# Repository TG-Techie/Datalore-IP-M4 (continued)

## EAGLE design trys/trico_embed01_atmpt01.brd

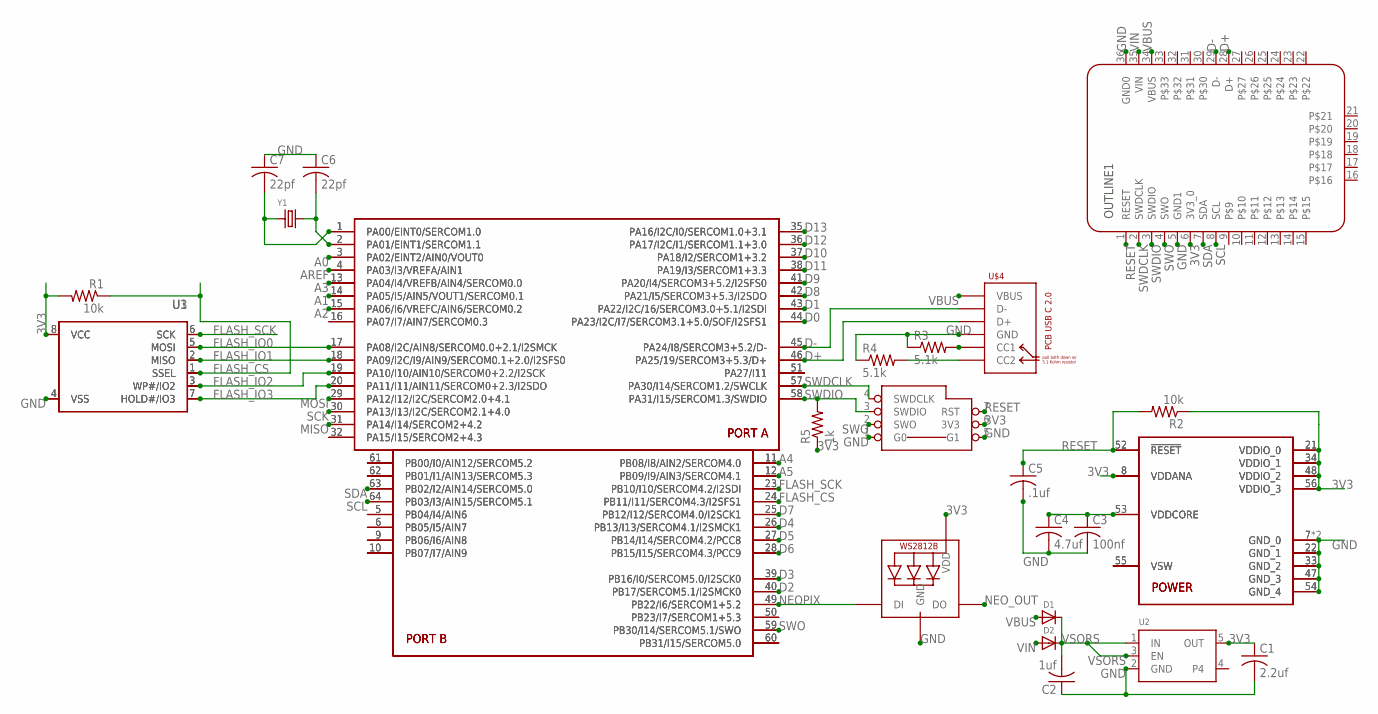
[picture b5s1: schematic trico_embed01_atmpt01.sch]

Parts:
C1: 2.2uf; TG-C0805MP
C2: 1uf; TG-C0805MP
C3: 100nf; TG-C0805MP
C4: 4.7uf; TG-C0805MP
C5: .1uf; TG-C0805MP
C6, C7: 22pf; TG-C0805MP
D1, D2: DIODESOD-123; SOD-123
LED1: LED-NEO-WS2812B3535; LED3535
OUTLINE1: TRIOC_DEV_36_EMBED_01BREAK; TRICO_DEV_01_BRK_HYBRID
R1, R2: 10k; TG-R0805
R3, R4: 5.1k; TG-R0805
R5: 1k; TG-R0805
U1: FLASH-SPI-SOIC8; SOIC8_150MIL
U2: VREG_STD_MIN_SOT23-5; SOT23-5
U3: FLASH-SPI-SOIC8208MIL; SOIC8_208MIL
U$1: MCU-ATSAMD51J-ADATQFP; QFP50P1200X1200X120-64N
U$2: MCU-ATSAMD51J-ADAADA; MICROBUILDER_PQFN64-1
U$3: SWD_POGO
U$4: USB-C-PCB-USB-2.0-TYPE-CDS_2; USB_TYPE_C_DS_2
Y1: XTAL_ADA4.9X1.8; MICROBUILDER_CRYSTAL_4.9X1.8

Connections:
3V3: C1.1, LED1.2 (VDD), OUTLINE1.6 (3V3_0), R1.2, R2.1, R5.1, U1.8 (VCC), U2.5 (OUT), U3.8 (VCC), U$1.8 (VDDANA), U$1.21 (VDDIO_0), U$1.34 (VDDIO_1), U$1.48 (VDDIO_2), U$1.56 (VDDIO_3), U$2.8 (VDDANA), U$2.21 (VDDIO_0), U$2.34 (VDDIO_1), U$2.48 (VDDIO_2), U$2.56 (VDDIO_3), U$3.6 (3V3)
A0: U$1.3 (PA02/EINT2/AIN0/VOUT0), U$2.3 (PA02/EINT2/AIN0/VOUT0)
A1: U$1.14 (PA05/I5/AIN5/VOUT1/SERCOM0.1), U$2.14 (PA05/I5/AIN5/VOUT1/SERCOM0.1)
A2: U$1.15 (PA06/I6/VREFC/AIN6/SERCOM0.2), U$2.15 (PA06/I6/VREFC/AIN6/SERCOM0.2)
A3: U$1.13 (PA04/I4/VREFB/AIN4/SERCOM0.0), U$2.13 (PA04/I4/VREFB/AIN4/SERCOM0.0)
A4: U$1.11 (PB08/I8/AIN2/SERCOM4.0), U$2.11 (PB08/I8/AIN2/SERCOM4.0)
A5: U$1.12 (PB09/I9/AIN3/SERCOM4.1), U$2.12 (PB09/I9/AIN3/SERCOM4.1)
AREF: U$1.4 (PA03/I3/VREFA/AIN1), U$2.4 (PA03/I3/VREFA/AIN1)
CC1: R3.2, U$4.A5 (CC1)
CC2: R4.2, U$4.B5 (CC2)
D0: U$1.44 (PA23/I2C/I7/SERCOM3.1+5.0/SOF/I2SFS1), U$2.44 (PA23/I2C/I7/SERCOM3.1+5.0/SOF/I2SFS1)
D1: U$1.43 (PA22/I2C/16/SERCOM3.0+5.1/I2SDI), U$2.43 (PA22/I2C/16/SERCOM3.0+5.1/I2SDI)
D2: U$1.40 (PB17/SERCOM5.1/I2SMCK0), U$2.40 (PB17/SERCOM5.1/I2SMCK0)
D3: U$1.39 (PB16/I0/SERCOM5.0/I2SCK0), U$2.39 (PB16/I0/SERCOM5.0/I2SCK0)
D4: U$1.26 (PB13/I13/SERCOM4.1/I2SMCK1), U$2.26 (PB13/I13/SERCOM4.1/I2SMCK1)
D5: U$1.27 (PB14/I14/SERCOM4.2/PCC8), U$2.27 (PB14/I14/SERCOM4.2/PCC8)
D6: U$1.28 (PB15/I15/SERCOM4.3/PCC9), U$2.28 (PB15/I15/SERCOM4.3/PCC9)
D7: U$1.25 (PB12/I12/SERCOM4.0/I2SCK1), U$2.25 (PB12/I12/SERCOM4.0/I2SCK1)
D8: U$1.42 (PA21/I5/SERCOM3+5.3/I2SDO), U$2.42 (PA21/I5/SERCOM3+5.3/I2SDO)
D9: U$1.41 (PA20/I4/SERCOM3+5.2/I2SFS0), U$2.41 (PA20/I4/SERCOM3+5.2/I2SFS0)
D10: U$1.37 (PA18/I2/SERCOM1+3.2), U$2.37 (PA18/I2/SERCOM1+3.2)
D11: U$1.38 (PA19/I3/SERCOM1+3.3), U$2.38 (PA19/I3/SERCOM1+3.3)
D12: U$1.36 (PA17/I2C/I1/SERCOM1.1+3.0), U$2.36 (PA17/I2C/I1/SERCOM1.1+3.0)
D13: U$1.35 (PA16/I2C/I0/SERCOM1.0+3.1), U$2.35 (PA16/I2C/I0/SERCOM1.0+3.1)
D+: OUTLINE1.28 (D+), U$1.46 (PA25/19/SERCOM3+5.3/D+), U$2.46 (PA25/19/SERCOM3+5.3/D+), U$4.A6 (D+), U$4.B6 (D+)
D-: OUTLINE1.29 (D-), U$1.45 (PA24/I8/SERCOM3+5.2/D-), U$2.45 (PA24/I8/SERCOM3+5.2/D-), U$4.A7 (D-), U$4.B7 (D-)
FLASH_CS: R1.1, U1.1 (SSEL), U3.1 (SSEL), U$1.24 (PB11/I11/SERCOM4.3/I2SFS1), U$2.24 (PB11/I11/SERCOM4.3/I2SFS1)
FLASH_IO0: U1.5 (MOSI), U3.5 (MOSI), U$1.17 (PA08/I2C/AIN8/SERCOM0.0+2.1/I2SMCK), U$2.17 (PA08/I2C/AIN8/SERCOM0.0+2.1/I2SMCK)
FLASH_IO1: U1.2 (MISO), U3.2 (MISO), U$1.18 (PA09/I2C/I9/AIN9/SERCOM0.1+2.0/I2SFS0), U$2.18 (PA09/I2C/I9/AIN9/SERCOM0.1+2.0/I2SFS0)
FLASH_IO2: U1.3 (WP#/IO2), U3.3 (WP#/IO2), U$1.19 (PA10/I10/AIN10/SERCOM0+2.2/I2SCK), U$2.19 (PA10/I10/AIN10/SERCOM0+2.2/I2SCK)
FLASH_IO3: U1.7 (HOLD#/IO3), U3.7 (HOLD#/IO3), U$1.20 (PA11/I11/AIN11/SERCOM0+2.3/I2SDO), U$2.20 (PA11/I11/AIN11/SERCOM0+2.3/I2SDO)
FLASH_SCK: U1.6 (SCK), U3.6 (SCK), U$1.23 (PB10/I10/SERCOM4.2/I2SDI), U$2.23 (PB10/I10/SERCOM4.2/I2SDI)
GND: C1.2, C2.1, C3.2, C4.2, C5.2, C6.1, C7.1, LED1.4 (GND), OUTLINE1.5 (GND1), OUTLINE1.36 (GND0), R3.1, R4.1, U1.4 (VSS), U2.2 (GND), U3.4 (VSS), U$1.7 (GND_0), U$1.22 (GND_1), U$1.33 (GND_2), U$1.47 (GND_3), U$1.54 (GND_4), U$2.7 (GND_0), U$2.22 (GND_1), U$2.33 (GND_2), U$2.47 (GND_3), U$2.54 (GND_4), U$2.EXP (GND_0), U$3.1 (G0), U$3.5 (G1), U$4.A1 (GND), U$4.A12 (GND), U$4.B1 (GND), U$4.B12 (GND)
MISO: U$1.31 (PA14/I14/SERCOM2+4.2), U$2.31 (PA14/I14/SERCOM2+4.2)
MOSI: U$1.29 (PA12/I12/I2C/SERCOM2.0+4.1), U$2.29 (PA12/I12/I2C/SERCOM2.0+4.1)
unnamed: U$1.16 (PA07/I7/AIN7/SERCOM0.3), U$2.16 (PA07/I7/AIN7/SERCOM0.3)
unnamed: U$1.32 (PA15/I15/SERCOM2+4.3), U$2.32 (PA15/I15/SERCOM2+4.3)
unnamed: U$1.51 (PA27/I11), U$2.51 (PA27/I11)
unnamed: U$1.61 (PB00/I0/AIN12/SERCOM5.2), U$2.61 (PB00/I0/AIN12/SERCOM5.2)
unnamed: U$1.62 (PB01/I1/AIN13/SERCOM5.3), U$2.62 (PB01/I1/AIN13/SERCOM5.3)
unnamed: U$1.5 (PB04/I4/AIN6), U$2.5 (PB04/I4/AIN6)
unnamed: U$1.6 (PB05/I5/AIN7), U$2.6 (PB05/I5/AIN7)
unnamed: U$1.9 (PB06/I6/AIN8), U$2.9 (PB06/I6/AIN8)
unnamed: U$1.10 (PB07/I7/AIN9), U$2.10 (PB07/I7/AIN9)
unnamed: U$1.50 (PB23/I7/SERCOM1+5.3), U$2.50 (PB23/I7/SERCOM1+5.3)
unnamed: U$1.60 (PB31/I15/SERCOM5.0), U$2.60 (PB31/I15/SERCOM5.0)
unnamed: U$1.55 (VSW), U$2.55 (VSW)
NEOPIX: LED1.1 (DI), U$1.49 (PB22/I6/SERCOM1+5.2), U$2.49 (PB22/I6/SERCOM1+5.2)
NEO_OUT: LED1.3 (DO)
RESET: C5.1, OUTLINE1.1 (RESET), R2.2, U$1.52 (!RESET), U$2.52 (!RESET), U$3.7 (RST)
SCK: U$1.30 (PA13/I13/I2C/SERCOM2.1+4.0), U$2.30 (PA13/I13/I2C/SERCOM2.1+4.0)
SCL: OUTLINE1.8 (SCL), U$1.64 (PB03/I3/AIN15/SERCOM5.1), U$2.64 (PB03/I3/AIN15/SERCOM5.1)
SDA: OUTLINE1.7 (SDA), U$1.63 (PB02/I2/AIN14/SERCOM5.0), U$2.63 (PB02/I2/AIN14/SERCOM5.0)
SWDCLK: OUTLINE1.2 (SWDCLK), U$1.57 (PA30/I14/SERCOM1.2/SWCLK), U$2.57 (PA30/I14/SERCOM1.2/SWCLK), U$3.4 (SWDCLK)
SWDIO: OUTLINE1.3 (SWDIO), R5.2, U$1.58 (PA31/I15/SERCOM1.3/SWDIO), U$2.58 (PA31/I15/SERCOM1.3/SWDIO), U$3.3 (SWDIO)
SWO: OUTLINE1.4 (SWO), U$1.59 (PB30/I14/SERCOM5.1/SWO), U$2.59 (PB30/I14/SERCOM5.1/SWO), U$3.2 (SWO)
VBUS: D1.A, OUTLINE1.34 (VBUS), U$4.A4 (VBUS), U$4.A9 (VBUS), U$4.B4 (VBUS), U$4.B9 (VBUS)
VCORE: C3.1, C4.1, U$1.53 (VDDCORE), U$2.53 (VDDCORE)
VIN: D2.A, OUTLINE1.35 (VIN)
VSORS: C2.2, D1.C, D2.C, U2.1 (IN), U2.3 (EN)
XTAL0: C6.2, U$1.2 (PA01/EINT1/SERCOM1.1), U$2.2 (PA01/EINT1/SERCOM1.1), Y1.2
XTAL1: C7.2, U$1.1 (PA00/EINT0/SERCOM1.0), U$2.1 (PA00/EINT0/SERCOM1.0), Y1.1

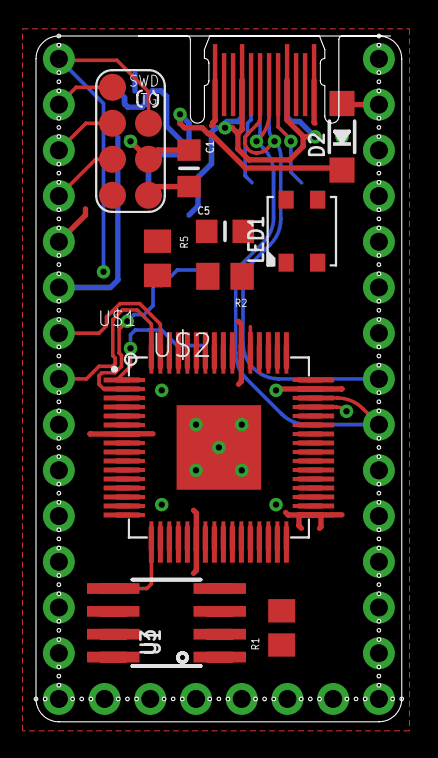
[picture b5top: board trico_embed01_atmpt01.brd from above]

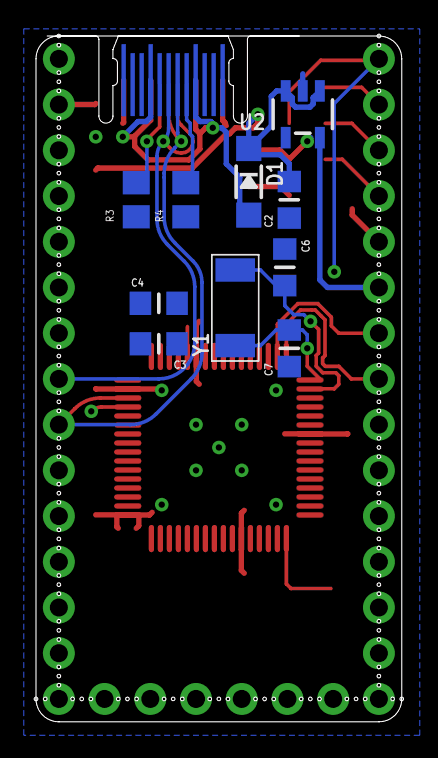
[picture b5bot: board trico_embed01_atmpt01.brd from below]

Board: 2 copper layers, 20.3 x 38.1 mm, 24 parts (10 on the bottom side), 61 nets.

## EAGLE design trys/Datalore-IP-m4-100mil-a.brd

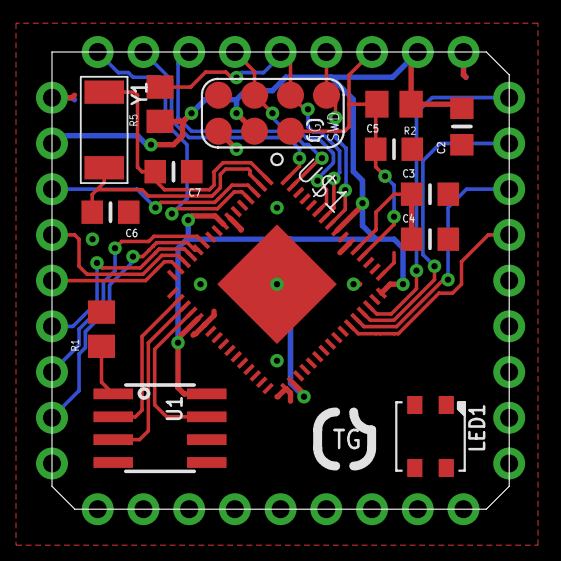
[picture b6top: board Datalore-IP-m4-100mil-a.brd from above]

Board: 2 copper layers, 25.4 x 25.4 mm, 16 parts (0 on the bottom side), 44 nets.

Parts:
C2: 1uf; TG-C0805MP
C3: 100nf; TG-C0805MP
C4: 4.7uf; TG-C0805MP
C5: .1uf; TG-C0805MP
C6, C7: 22pf; TG-C0805MP
LED1: LED-NEO-WS2812B3535; LED3535
PKG1: DL_IP_36-100MIL-PACKAGE
R1, R2: 10k; TG-R0805
R5: 1k; TG-R0805
U1: SOIC8_150MIL
U$1: MCU-ATSAMD51J-ADAADA; MICROBUILDER_PQFN64-1
U$4: SWD_POGO
U$5: LOGO-TG_TECHIEBIG?; LOGO_TG_TEST_LARGE
Y1: MICROBUILDER_CRYSTAL_4.9X1.8

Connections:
3V3: C2.2, LED1.2, PKG1.8, PKG1.35, R1.2, R2.1, R5.1, U1.8, U$1.8, U$1.21, U$1.34, U$1.48, U$1.56, U$4.6
A0: PKG1.34, U$1.3
A1: PKG1.33, U$1.14
A2: PKG1.32, U$1.15
A3: PKG1.31, U$1.13
A4: PKG1.30, U$1.11
A5: PKG1.29, U$1.12
AREF: PKG1.1, U$1.4
D0: PKG1.12, U$1.44
D1: PKG1.13, U$1.43
D2: PKG1.14, U$1.40
D3: PKG1.15, U$1.39
D4: PKG1.16, U$1.26
D5: PKG1.17, U$1.27
D6: PKG1.18, U$1.28
D7: PKG1.22, U$1.25
D8: PKG1.23, U$1.42
D9: PKG1.24, U$1.41
D10: PKG1.25, U$1.37
D11: PKG1.26, U$1.38
D12: PKG1.27, U$1.36
D13: PKG1.28, U$1.35
D+: PKG1.10, U$1.46
D-: PKG1.11, U$1.45
FLASH_CS: R1.1, U1.1, U$1.24
FLASH_IO0: U1.5, U$1.17
FLASH_IO1: U1.2, U$1.18
FLASH_IO2: U1.3, U$1.19
FLASH_IO3: U1.7, U$1.20
FLASH_SCK: U1.6, U$1.23
GND: C2.1, C3.2, C4.2, C5.2, C6.1, C7.1, LED1.4, PKG1.9, PKG1.36, U1.4, U$1.7, U$1.22, U$1.33, U$1.47, U$1.54, U$1.EXP, U$4.1, U$4.5
MISO: PKG1.19, U$1.31
MOSI: PKG1.21, U$1.29
NEOPIX: LED1.1, U$1.49
RESET: C5.1, PKG1.7, R2.2, U$1.52, U$4.7
SCK: PKG1.20, U$1.30
SCL: PKG1.2, U$1.64
SDA: PKG1.3, U$1.63
SWDCLK: PKG1.6, U$1.57, U$4.4
SWDIO: PKG1.5, R5.2, U$1.58, U$4.3
SWO: PKG1.4, U$1.59, U$4.2
VCORE: C3.1, C4.1, U$1.53
XTAL0: C6.2, U$1.2, Y1.2
XTAL1: C7.2, U$1.1, Y1.1

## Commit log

2018-12-08 first commit to transfer files
2018-12-10 stated mother board
